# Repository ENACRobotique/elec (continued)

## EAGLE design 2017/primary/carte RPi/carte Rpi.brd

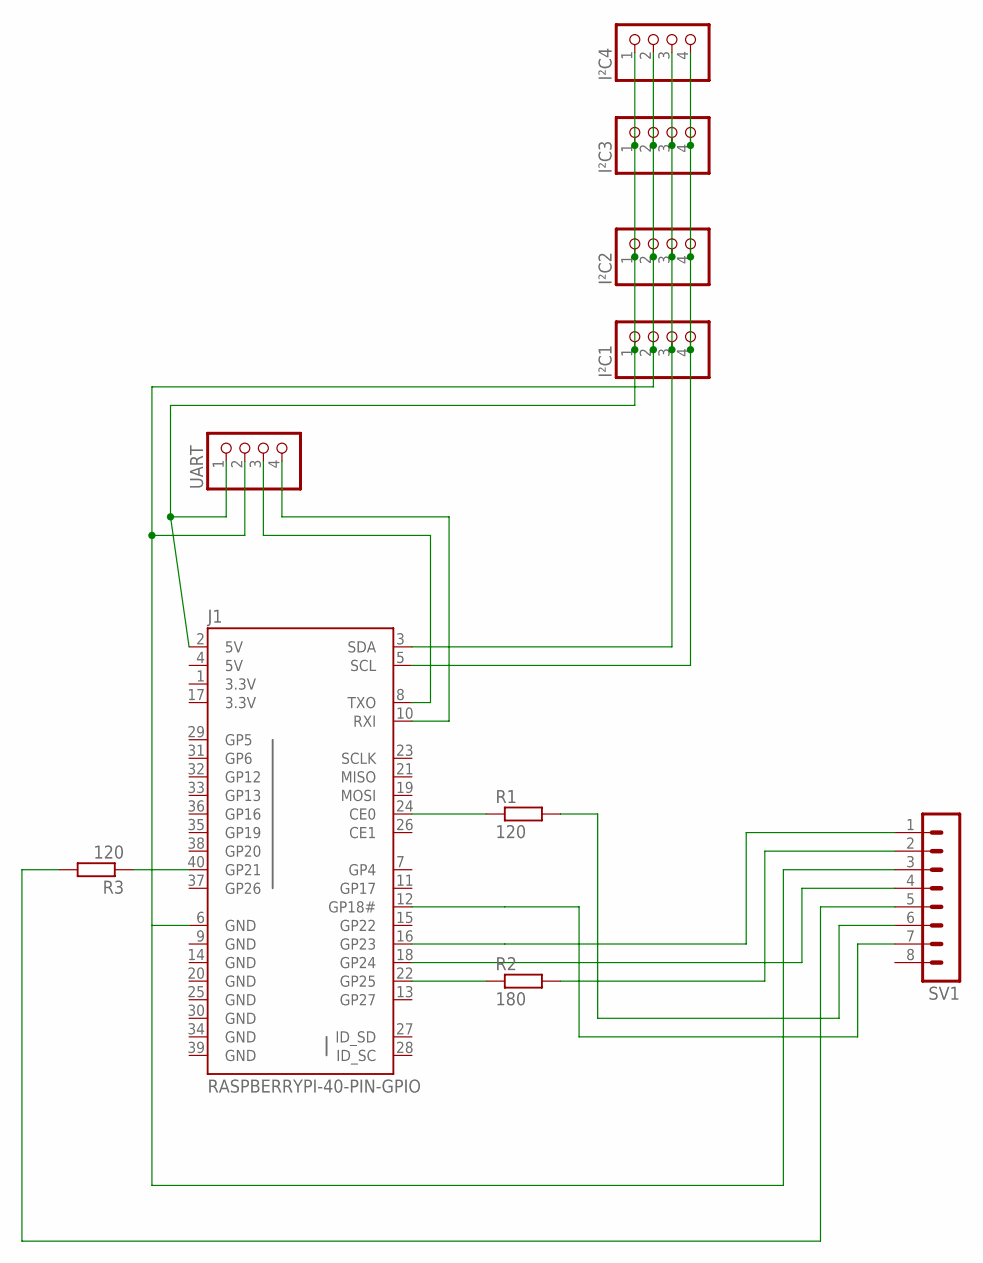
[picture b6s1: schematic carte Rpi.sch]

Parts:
I²C1, I²C2, I²C3, I²C4: PINHD-1X4; 1X04
J1: RASPBERRYPI-40-PIN-GPIO; 2X20-SHROUDED
R1, R3: 120; 0207/10
R2: 180; 0207/10
SV1: MA08-1
UART: PINHD-1X4; 1X04

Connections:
3.3V: J1.1 (3.3V), J1.17 (3.3V)
5V: I²C1.1, I²C2.1, I²C3.1, I²C4.1, J1.2 (5V), J1.4 (5V), UART.1
GND: I²C1.2, I²C2.2, I²C3.2, I²C4.2, J1.6 (GND), J1.9 (GND), J1.14 (GND), J1.20 (GND), J1.25 (GND), J1.30 (GND), J1.34 (GND), J1.39 (GND), SV1.3, UART.2
LED_BLUE: R3.2, SV1.5
LED_GREEN: R1.2, SV1.6
LED_RED: R2.2, SV1.2
unnamed: J1.24 (CE0), R1.1
unnamed: J1.22 (GP25), R2.1
unnamed: J1.40 (GP21), R3.1
PULL_UP_BUTTON1: J1.18 (GP24), SV1.4
PULL_UP_BUTTON2: J1.12 (GP18#), SV1.7
PULL_UP_TIRETTE: J1.16 (GP23), SV1.1
RX: J1.10 (RXI), UART.4
SCL: I²C1.4, I²C2.4, I²C3.4, I²C4.4, J1.5 (SCL)
SDA: I²C1.3, I²C2.3, I²C3.3, I²C4.3, J1.3 (SDA)
TX: J1.8 (TXO), UART.3

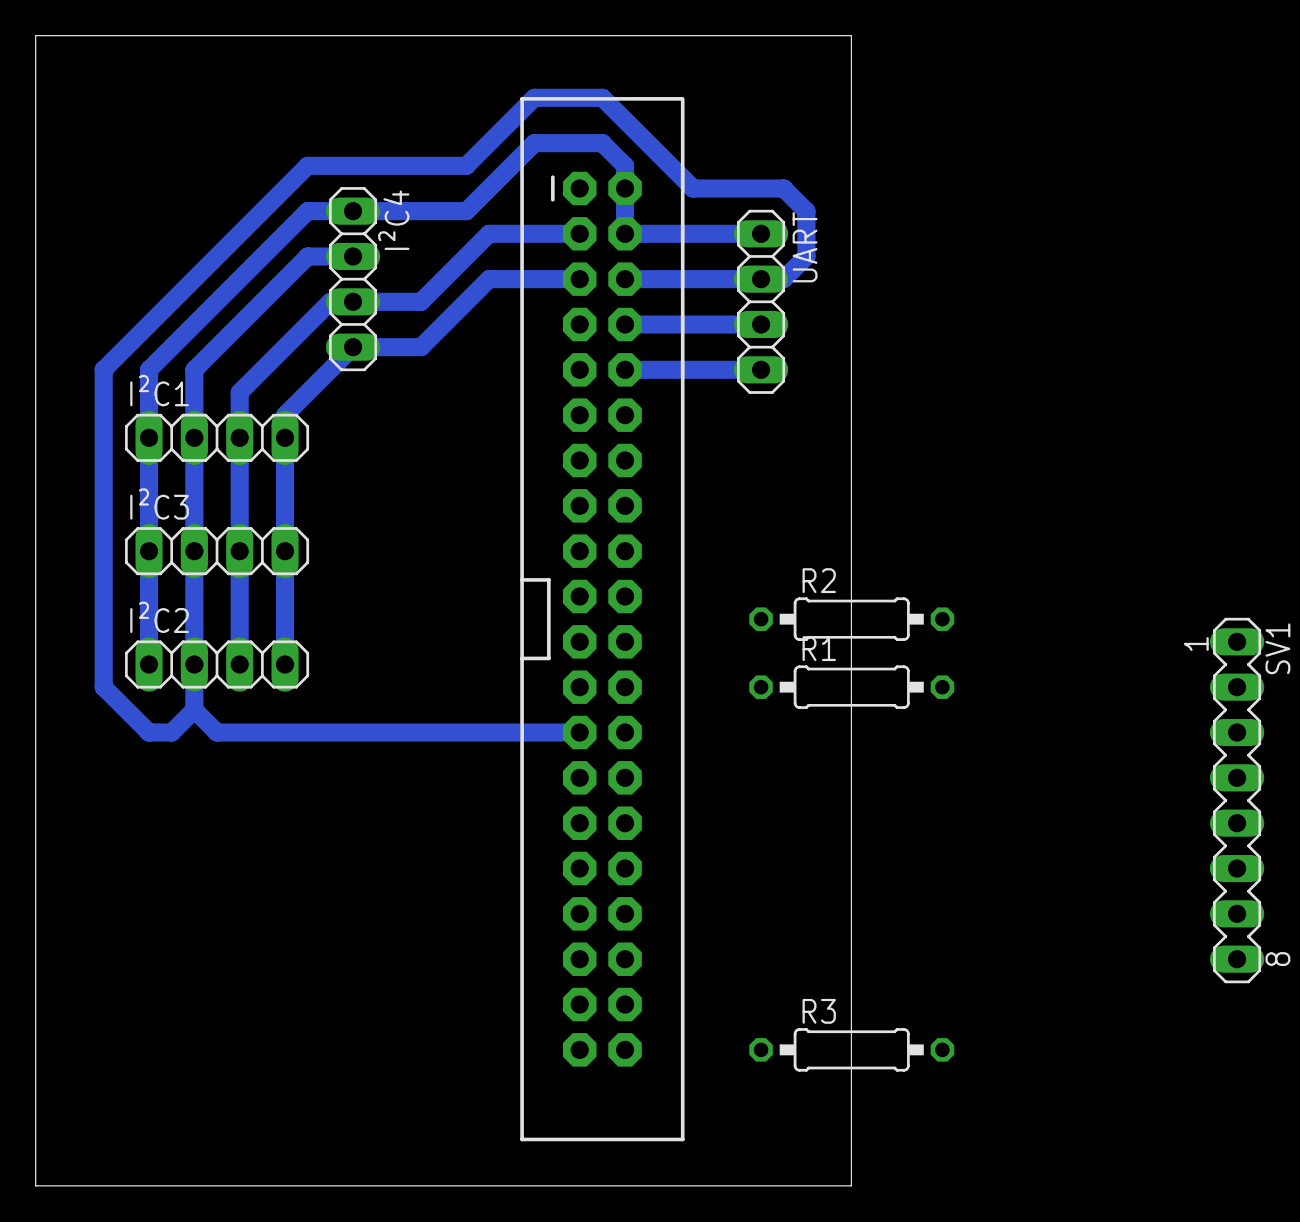
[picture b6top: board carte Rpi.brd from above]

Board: 2 copper layers, 45.7 x 64.4 mm, 10 parts (0 on the bottom side), 16 nets.

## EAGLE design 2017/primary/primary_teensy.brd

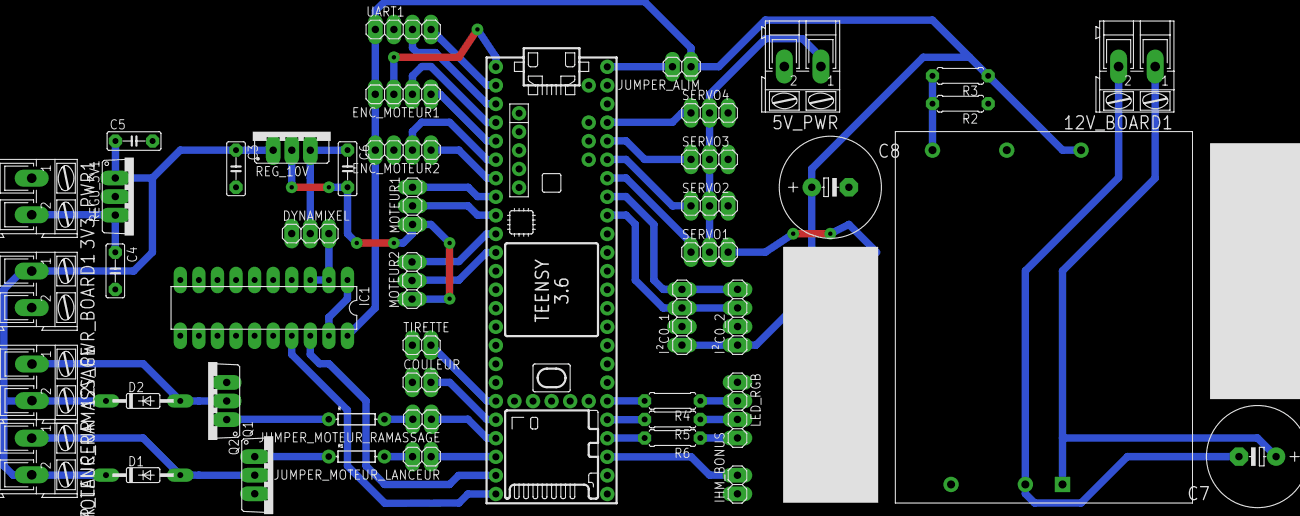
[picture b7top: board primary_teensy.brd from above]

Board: 2 copper layers, 47 parts (0 on the bottom side), 47 nets.

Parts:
3V3_PWR1, 5V_PWR, 12V_BOARD1, 12V_PWR_BOARD1: AK300/2
C3, C5: 0.1uF; C050-025X075
C4, C6: 10uF; C050-025X075
C7, C8: 2.2m; E5-13
COULEUR: 1X02
D1, D2: 1N4148DO35-10; DO35-10
DYNAMIXEL: 1X03
ENC_MOTEUR1, ENC_MOTEUR2: 1X04
IC1: 74LS241N; DIL20
IHM_BONUS: 1X02
I²C0_1, I²C0_2: 1X04
JUMPER_ALIM: 1X02
JUMPER_MOTEUR_LANCEUR: 1X02
JUMPER_MOTEUR_RAMASSAGE: 1X02
LED_RGB: 1X04
MOTEUR1, MOTEUR2: 1X03
MOTEUR_LANCEUR: AK300/2
MOTEUR_RAMASSAGE: AK300/2
Q1, Q2: MFR475V; TO220AV
R, R1: AXIAL-0.3
R2: 3.3k; 0207/7
R3: 2.7k; 0207/7
R4, R5, R6: 0207/7
REGU_3V1: 7805TV; TO220V
REG_10V: 10; 78XXS
SERVO1, SERVO2, SERVO3, SERVO4: 1X03
TIRETTE: 1X02
U$1: TEENSY_3.5/3.6
U$3: TEN25-1211TEN25-1211; TEN25
UART1: 1X04

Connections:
3V3: 3V3_PWR1.2, C4.1, REGU_3V1.3
5V_PWR: 5V_PWR.1, SERVO1.2, SERVO2.2, SERVO3.2, SERVO4.2
5V_SIG: C8.+, ENC_MOTEUR1.4, ENC_MOTEUR2.4, IC1.20, I²C0_1.1, I²C0_2.1, JUMPER_ALIM.1, R3.1, U$3.5, UART1.1
10V_PWR: C6.1, DYNAMIXEL.2, REG_10V.OUT
12V_PWR: 12V_PWR_BOARD1.1, C3.1, C5.1, D1.C, D2.C, MOTEUR_LANCEUR.2, MOTEUR_RAMASSAGE.2, REGU_3V1.1, REG_10V.IN
+12V: 12V_BOARD1.1, C7.+, U$3.1
ENC_MOT1_A: ENC_MOTEUR1.2, U$1.2
ENC_MOT1_B: ENC_MOTEUR1.1, U$1.3/CANTX
ENC_MOT2_A: ENC_MOTEUR2.2, U$1.4/CANRX
ENC_MOT2_B: ENC_MOTEUR2.1, U$1.5
GND: 3V3_PWR1.1, 5V_PWR.2, 12V_PWR_BOARD1.2, C3.2, C4.2, C5.2, C6.2, C8.-, COULEUR.1, DYNAMIXEL.1, ENC_MOTEUR1.3, ENC_MOTEUR2.3, IC1.10, IHM_BONUS.1, I²C0_1.2, I²C0_2.2, LED_RGB.1, MOTEUR1.1, MOTEUR2.1, Q1.E, Q2.E, R2.1, REGU_3V1.2, REG_10V.GND, SERVO1.3, SERVO2.3, SERVO3.3, SERVO4.3, TIRETTE.1, U$1.GND, U$3.6, UART1.2
GND_12: 12V_BOARD1.2, C7.-, U$3.2
MOT1_DIR: MOTEUR1.3, U$1.6
MOT1_PWM: MOTEUR1.2, U$1.7
MOT2_DIR: MOTEUR2.3, U$1.8
MOT2_PWM: MOTEUR2.2, U$1.9/CS
MOT_LANCEUR: JUMPER_MOTEUR_LANCEUR.1, U$1.30
MOT_RAMASSAGE: JUMPER_MOTEUR_RAMASSAGE.1, U$1.29
unnamed: D2.A, MOTEUR_RAMASSAGE.1, Q1.C
unnamed: D1.A, MOTEUR_LANCEUR.1, Q2.C
unnamed: LED_RGB.4, R6.1
unnamed: R2.2, R3.2, U$3.7
unnamed: Q2.B, R1.P$1
unnamed: Q1.B, R.P$1
unnamed: LED_RGB.3, R5.1
unnamed: JUMPER_MOTEUR_LANCEUR.2, R1.P$2
unnamed: JUMPER_MOTEUR_RAMASSAGE.2, R.P$2
unnamed: SERVO4.1, U$1.23/A9
unnamed: LED_RGB.2, R4.1
unnamed: SERVO3.1, U$1.22/A8
unnamed: SERVO2.1, U$1.21/A7
unnamed: SERVO1.1, U$1.20/A6
unnamed: JUMPER_ALIM.2, U$1.VIN
unnamed: COULEUR.2, U$1.28
unnamed: R4.2, U$1.38/A19
unnamed: R5.2, U$1.37/A18
unnamed: R6.2, U$1.36/A17
unnamed: IHM_BONUS.2, U$1.35/A16
unnamed: I²C0_1.3, I²C0_2.3, U$1.18/A4/SDA
unnamed: I²C0_1.4, I²C0_2.4, U$1.19/A5/SCL
unnamed: TIRETTE.2, U$1.27
unnamed: IC1.1, IC1.19
unnamed: DYNAMIXEL.3, IC1.2, IC1.3
RX0: U$1.0/RX, UART1.4
RX4: IC1.18, U$1.31/A12
TX1: U$1.1/TX, UART1.3
TX4: IC1.17, U$1.32/A13

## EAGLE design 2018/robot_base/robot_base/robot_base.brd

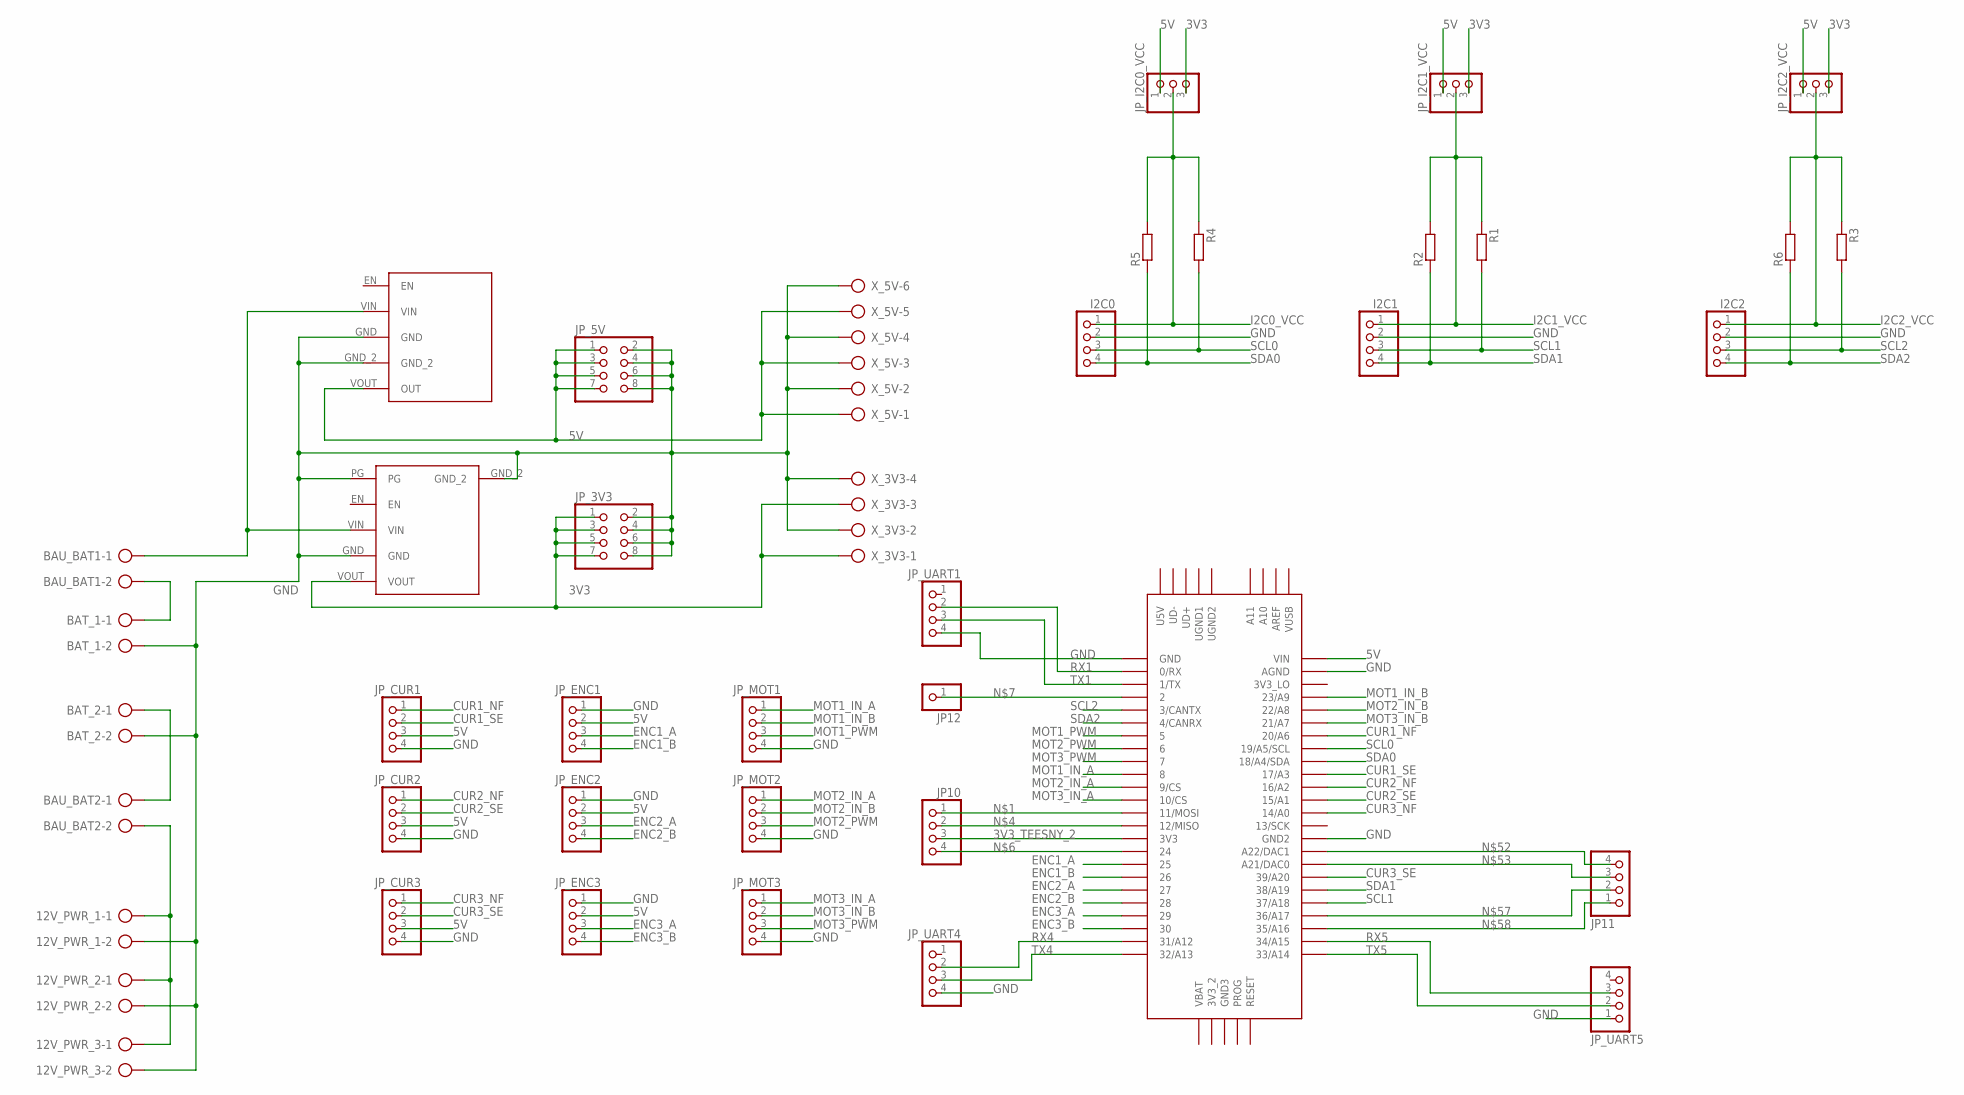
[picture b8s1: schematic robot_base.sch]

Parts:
12V_PWR_1, 12V_PWR_2, 12V_PWR_3: AK500/2
BAT_1, BAT_2: AK500/2
BAU_BAT1, BAU_BAT2: AK500/2
D24V22F3: D24V22F3
D24V50F5: D24V50F5
I2C0, I2C1, I2C2: PINHD-1X4; 1X04
JP10, JP11: PINHD-1X4; 1X04
JP12: PINHD-1X1; 1X01
JP_3V3, JP_5V: PINHD-2X4; 2X04
JP_CUR1, JP_CUR2, JP_CUR3: PINHD-1X4; 1X04
JP_ENC1, JP_ENC2, JP_ENC3: PINHD-1X4; 1X04
JP_I2C0_VCC, JP_I2C1_VCC, JP_I2C2_VCC: PINHD-1X3; 1X03
JP_MOT1, JP_MOT2, JP_MOT3: PINHD-1X4; 1X04
JP_UART1, JP_UART4, JP_UART5: PINHD-1X4; 1X04
R1, R2, R3, R4, R5, R6: R-EU_0204/5; 0204/5
U$1: TEENSY_3.5/3.6TEENSY_3.5/3.6_LONG_PADS; TEENSY_3.5/3.6
X_3V3: AK300/4
X_5V: AK300/6

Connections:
3V3: D24V22F3.VOUT, JP_3V3.1, JP_3V3.3, JP_3V3.5, JP_3V3.7, JP_I2C0_VCC.3, JP_I2C1_VCC.3, JP_I2C2_VCC.3, X_3V3.1, X_3V3.3
3V3_TEESNY_2: JP10.3, U$1.3V3
5V: D24V50F5.VOUT (OUT), JP_5V.1, JP_5V.3, JP_5V.5, JP_5V.7, JP_CUR1.3, JP_CUR2.3, JP_CUR3.3, JP_ENC1.2, JP_ENC2.2, JP_ENC3.2, JP_I2C0_VCC.1, JP_I2C1_VCC.1, JP_I2C2_VCC.1, U$1.VIN, X_5V.1, X_5V.3, X_5V.5
CUR1_NF: JP_CUR1.1, U$1.20/A6
CUR1_SE: JP_CUR1.2, U$1.17/A3
CUR2_NF: JP_CUR2.1, U$1.16/A2
CUR2_SE: JP_CUR2.2, U$1.15/A1
CUR3_NF: JP_CUR3.1, U$1.14/A0
CUR3_SE: JP_CUR3.2, U$1.39/A20
ENC1_A: JP_ENC1.3, U$1.25
ENC1_B: JP_ENC1.4, U$1.26
ENC2_A: JP_ENC2.3, U$1.27
ENC2_B: JP_ENC2.4, U$1.28
ENC3_A: JP_ENC3.3, U$1.29
ENC3_B: JP_ENC3.4, U$1.30
GND: 12V_PWR_1.2, 12V_PWR_2.2, 12V_PWR_3.2, BAT_1.2, BAT_2.2, D24V22F3.GND, D24V22F3.GND_2, D24V22F3.PG, D24V50F5.GND, D24V50F5.GND_2, I2C0.2, I2C1.2, I2C2.2, JP_3V3.2, JP_3V3.4, JP_3V3.6, JP_3V3.8, JP_5V.2, JP_5V.4, JP_5V.6, JP_5V.8, JP_CUR1.4, JP_CUR2.4, JP_CUR3.4, JP_ENC1.1, JP_ENC2.1, JP_ENC3.1, JP_MOT1.4, JP_MOT2.4, JP_MOT3.4, JP_UART1.4, JP_UART4.4, JP_UART5.1, U$1.AGND, U$1.GND, U$1.GND2, X_3V3.2, X_3V3.4, X_5V.2, X_5V.4, X_5V.6
I2C0_VCC: I2C0.1, JP_I2C0_VCC.2, R4.1, R5.2
I2C1_VCC: I2C1.1, JP_I2C1_VCC.2, R1.1, R2.2
I2C2_VCC: I2C2.1, JP_I2C2_VCC.2, R3.1, R6.2
MOT1_IN_A: JP_MOT1.1, U$1.8
MOT1_IN_B: JP_MOT1.2, U$1.23/A9
MOT1_PWM: JP_MOT1.3, U$1.5
MOT2_IN_A: JP_MOT2.1, U$1.9/CS
MOT2_IN_B: JP_MOT2.2, U$1.22/A8
MOT2_PWM: JP_MOT2.3, U$1.6
MOT3_IN_A: JP_MOT3.1, U$1.10/CS
MOT3_IN_B: JP_MOT3.2, U$1.21/A7
MOT3_PWM: JP_MOT3.3, U$1.7
unnamed: JP10.1, U$1.11/MOSI
unnamed: 12V_PWR_1.1, 12V_PWR_2.1, 12V_PWR_3.1, BAU_BAT2.2
unnamed: BAT_2.1, BAU_BAT2.1
unnamed: JP10.2, U$1.12/MISO
unnamed: BAU_BAT1.1, D24V22F3.VIN, D24V50F5.VIN
unnamed: JP10.4, U$1.24
unnamed: JP12.1, U$1.2
unnamed: BAT_1.1, BAU_BAT1.2
unnamed: JP11.4, U$1.A22/DAC1
unnamed: JP11.3, U$1.21/DAC0 (A21/DAC0)
unnamed: JP11.2, U$1.36/A17
unnamed: JP11.1, U$1.35/A16
RX1: JP_UART1.2, U$1.0/RX
RX4: JP_UART4.2, U$1.31/A12
RX5: JP_UART5.3, U$1.34/A15
SCL0: I2C0.3, R4.2, U$1.19/A5/SCL
SCL1: I2C1.3, R1.2, U$1.37/A18
SCL2: I2C2.3, R3.2, U$1.3/CANTX
SDA0: I2C0.4, R5.1, U$1.18/A4/SDA
SDA1: I2C1.4, R2.1, U$1.38/A19
SDA2: I2C2.4, R6.1, U$1.4/CANRX
TX1: JP_UART1.3, U$1.1/TX
TX4: JP_UART4.3, U$1.32/A13
TX5: JP_UART5.2, U$1.33/A14

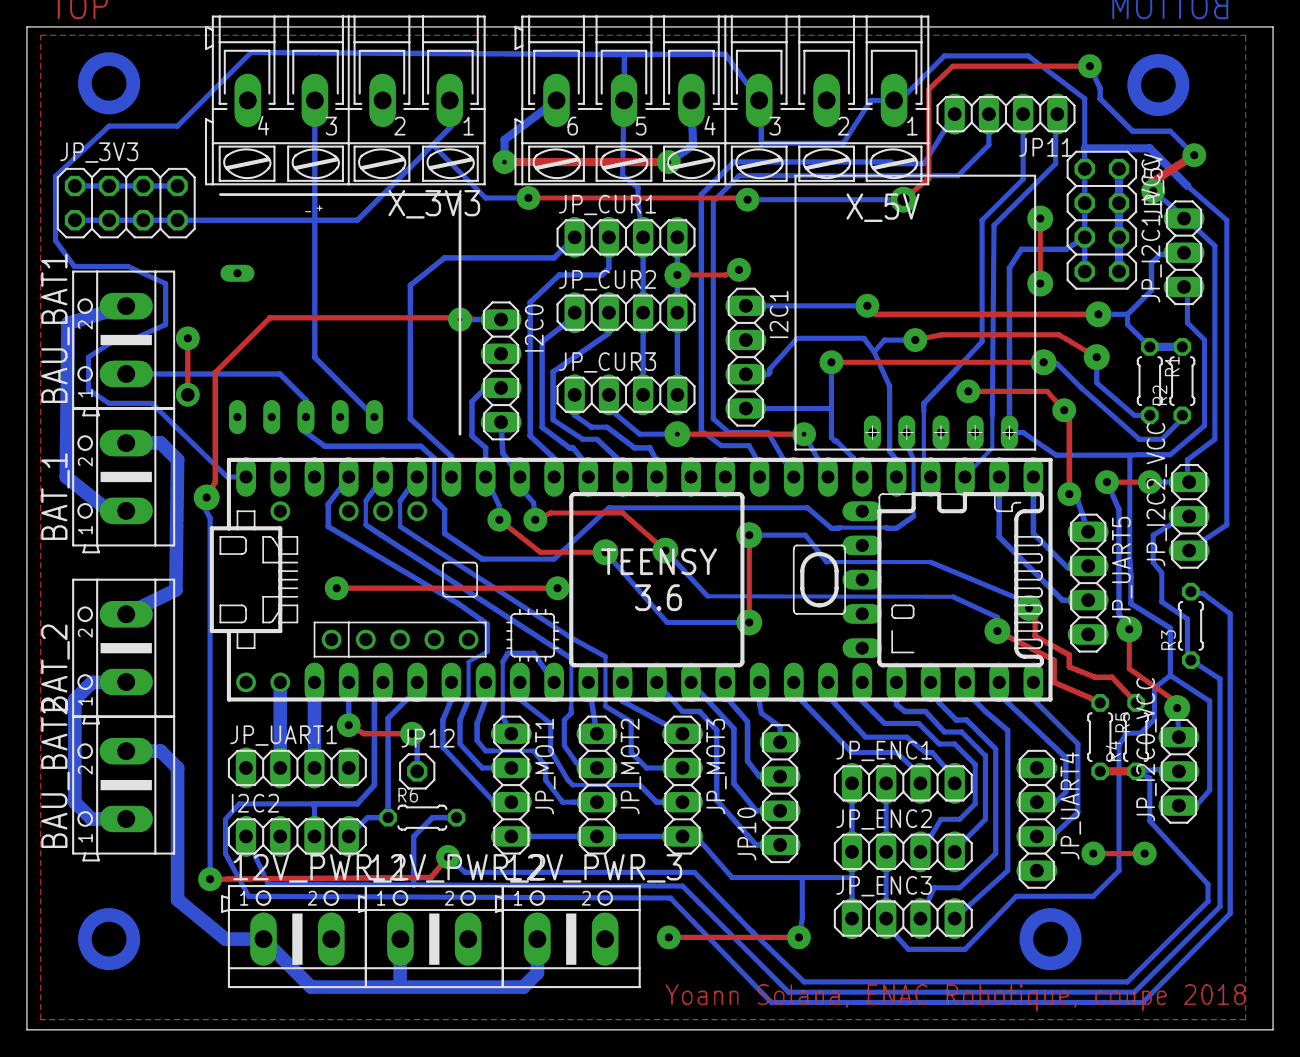
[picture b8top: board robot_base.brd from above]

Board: 2 copper layers, 92.5 x 74.4 mm, 41 parts (0 on the bottom side), 52 nets.
